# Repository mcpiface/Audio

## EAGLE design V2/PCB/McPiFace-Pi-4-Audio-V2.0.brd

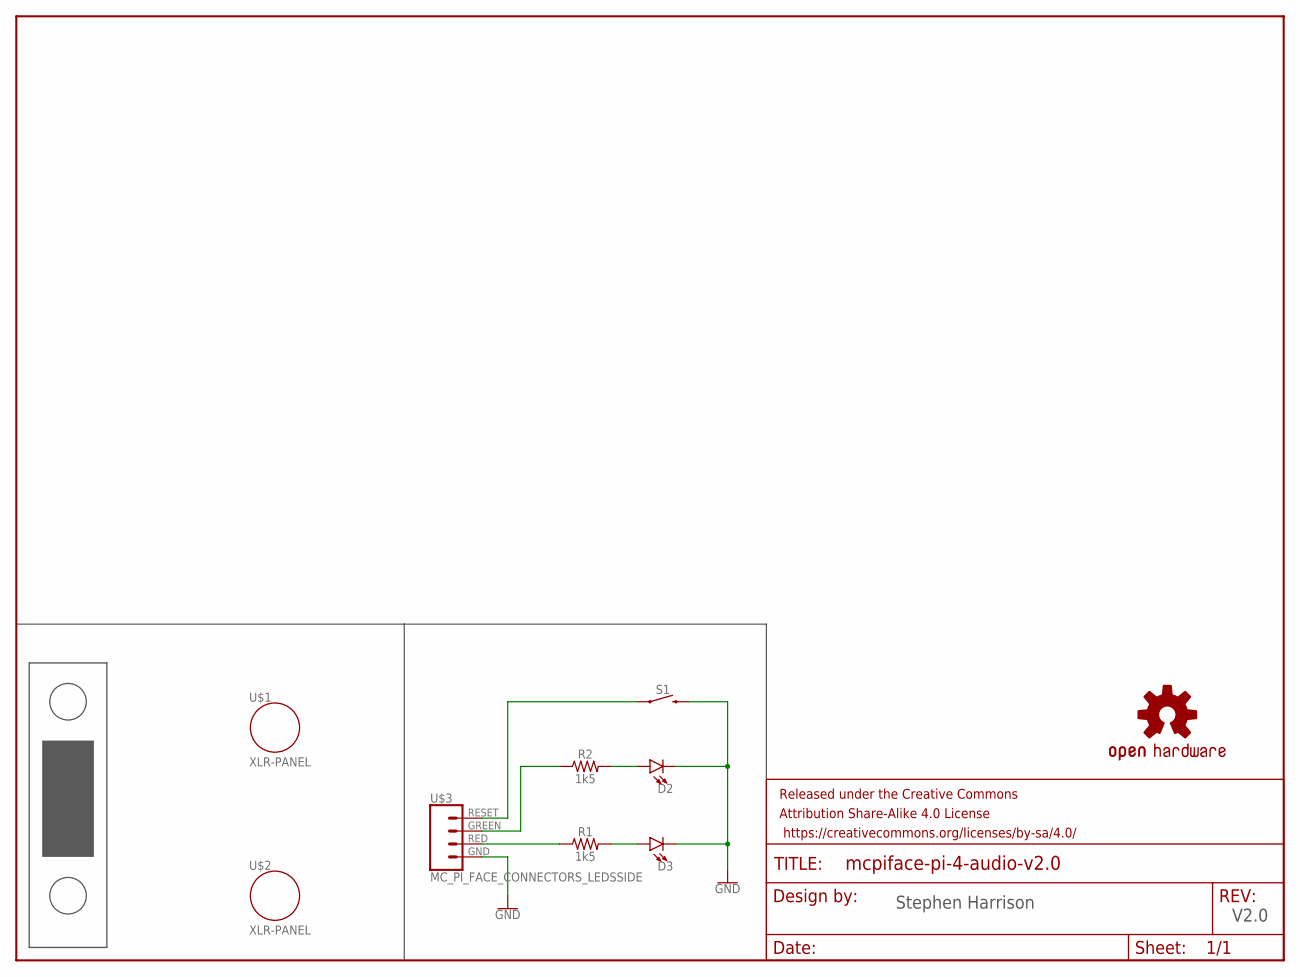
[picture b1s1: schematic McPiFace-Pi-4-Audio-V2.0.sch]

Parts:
D2: LEDLED-1206-BOTTOM-2.0MM-GREEN; LED-1206-BOTTOM-2.0MM
D3: LEDLED-1206-BOTTOM-2.0MM-RED; LED-1206-BOTTOM-2.0MM
FRAME1: FRAME-LETTER; CREATIVE_COMMONS
LOGO1: OSHW-LOGOL; OSHW-LOGO-L
R1, R2: 1k5; 0805
S1: MOMENTARY-SWITCH-SPSTTACKTILE_SWITCH_PTH_6.0MM_NO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; TACTILE_SWITCH_PTH_6.0MM_NO_TOP_RESIST
U$1, U$2: XLR-PANEL; NC3FD-V-BAG-PANEL-COUTOUT
U$3: MC_PI_FACE_CONNECTORS_LEDSSIDE; JST-4-SH-1.0MM-SIDE
U$4: MC_PI_4_FACE_PANELDOUBLE; MC_PI_4-DOUBLE_FACE

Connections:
GND: D2.C, D3.C, S1.3 (2), U$3.GND
unnamed: D2.A, R2.2
unnamed: D3.A, R1.2
unnamed: R1.1, U$3.RED
unnamed: R2.1, U$3.GREEN
unnamed: S1.1, U$3.RESET

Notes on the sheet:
V2.0
Stephen Harrison

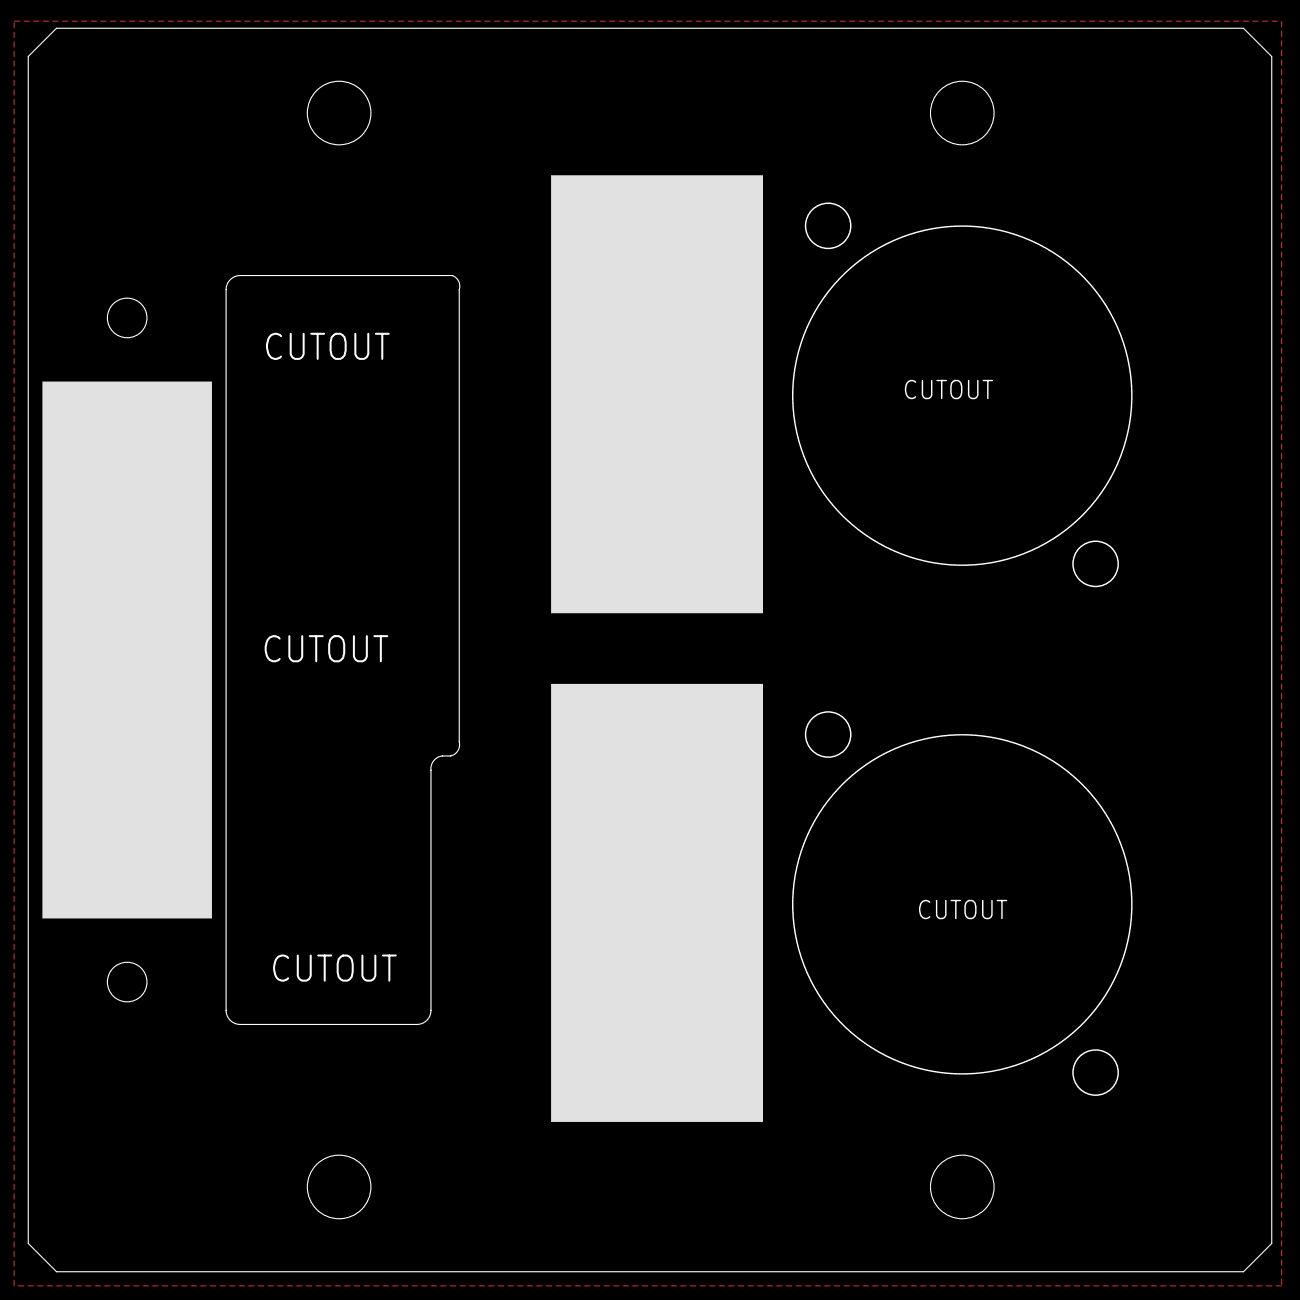
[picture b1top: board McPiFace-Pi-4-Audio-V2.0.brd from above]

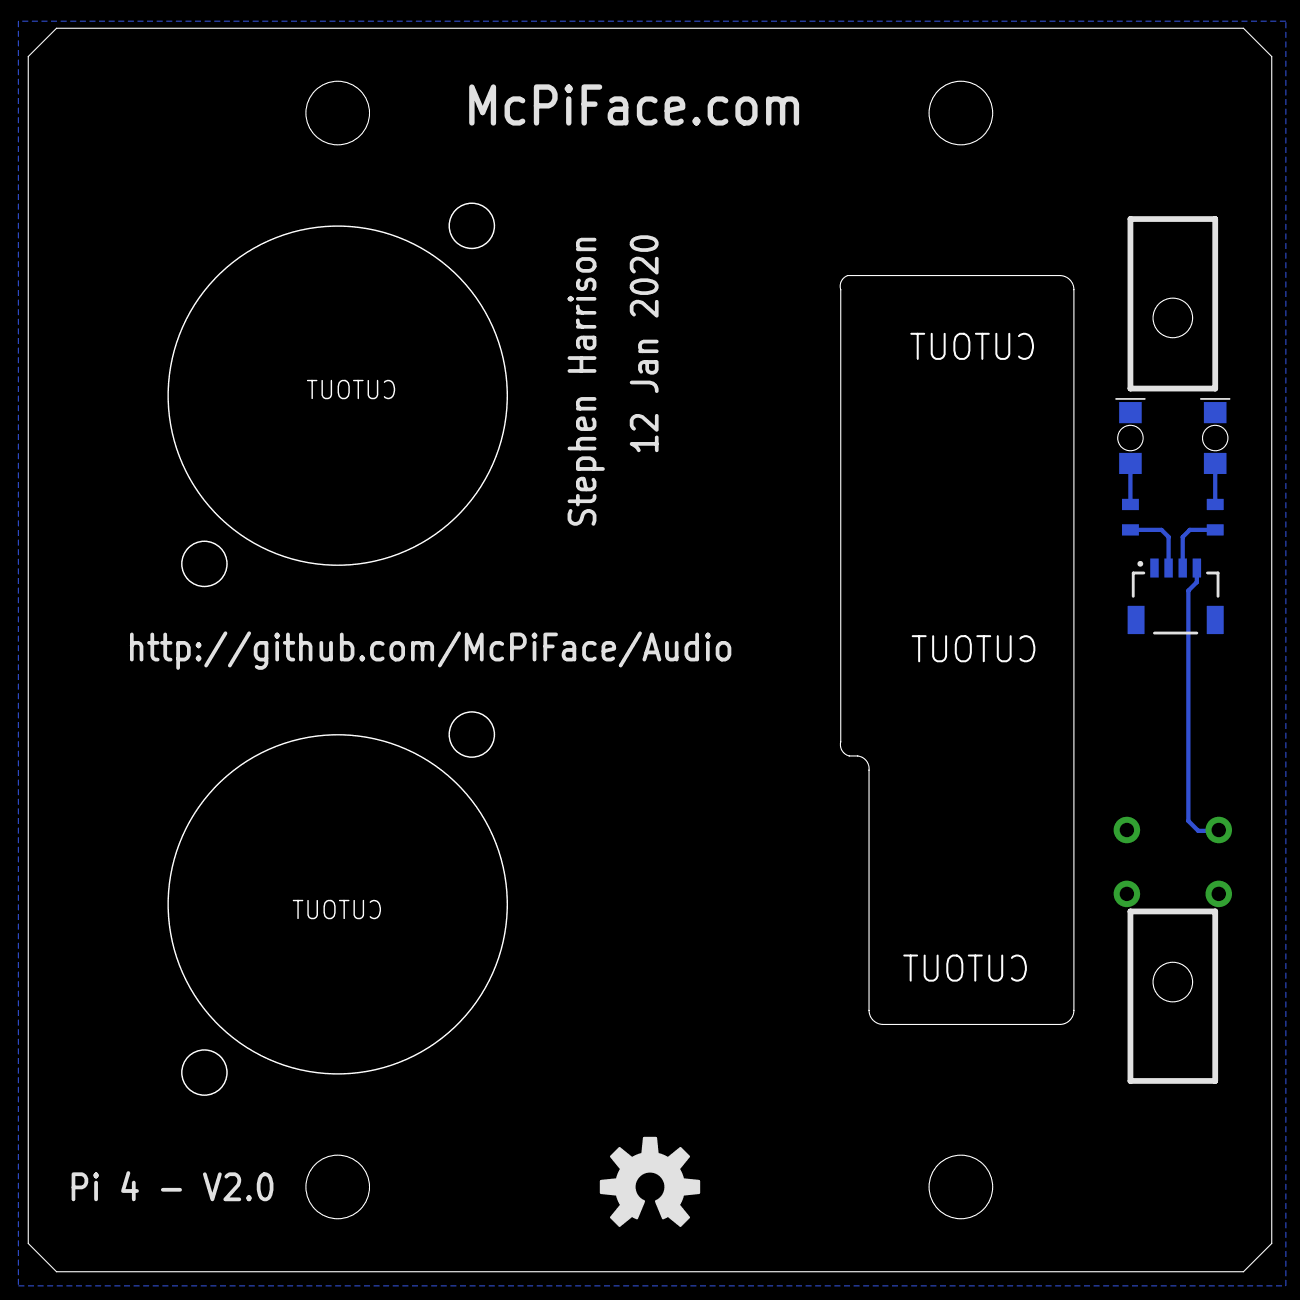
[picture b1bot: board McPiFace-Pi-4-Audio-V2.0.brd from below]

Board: 2 copper layers, 88.0 x 88.0 mm, 11 parts (6 on the bottom side), 6 nets.

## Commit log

2019-03-13 Initial version.
2020-01-12 V2 for the Pi 4.
    Note: Date incorrect on bottom silk.
    As sent to JLCPCB.
2020-01-12 Adding V1 images.
2020-01-12 Fixed V2 filenames.
2020-01-12 Fixed date/version numbers.

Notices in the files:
parts and their libraries:
SparkFun-Aesthetics: Licensing: Creative Commons ShareAlike 4.0 International - https://creativecommons.org/licenses/by-sa/4.0
SparkFun-Aesthetics: Released under the Creative Commons Attribution Share-Alike 4.0 License
SparkFun-Aesthetics: https://creativecommons.org/licenses/by-sa/4.0
